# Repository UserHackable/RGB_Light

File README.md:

## RGB_Light 

### Board dimensions

* (120000, 140000) original units
* (1.2000, 1.4000) inches
* (30.4800, 35.5600) mm

[gerbers](%*_gerber.zip)

| Front | Back |
| --- | --- |
|  |  |

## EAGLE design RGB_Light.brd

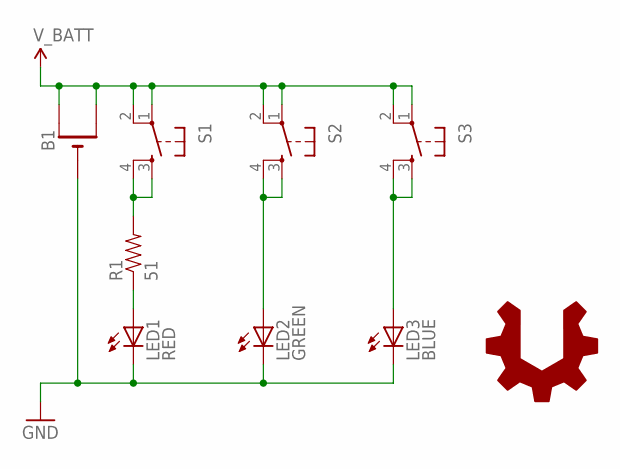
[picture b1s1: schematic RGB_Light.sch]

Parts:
B1: CR2032THM; CR2032-THRU
LED1: RED; LED5MM
LED2: GREEN; LED5MM
LED3: BLUE; LED5MM
R1: 51; AXIAL-0.3
S1, S2, S3: TAC_SWITCHPTH; TACTILE-PTH
U$1: USER_HACKABLE

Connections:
GND: B1.-, LED1.K (C), LED2.K (C), LED3.K (C)
unnamed: LED2.A, S2.3, S2.4
unnamed: R1.P$2 (2), S1.3, S1.4
unnamed: LED3.A, S3.3, S3.4
unnamed: LED1.A, R1.P$1 (1)
V_BATT: B1.+1 (+), B1.+2 (+1), S1.1, S1.2, S2.1, S2.2, S3.1, S3.2

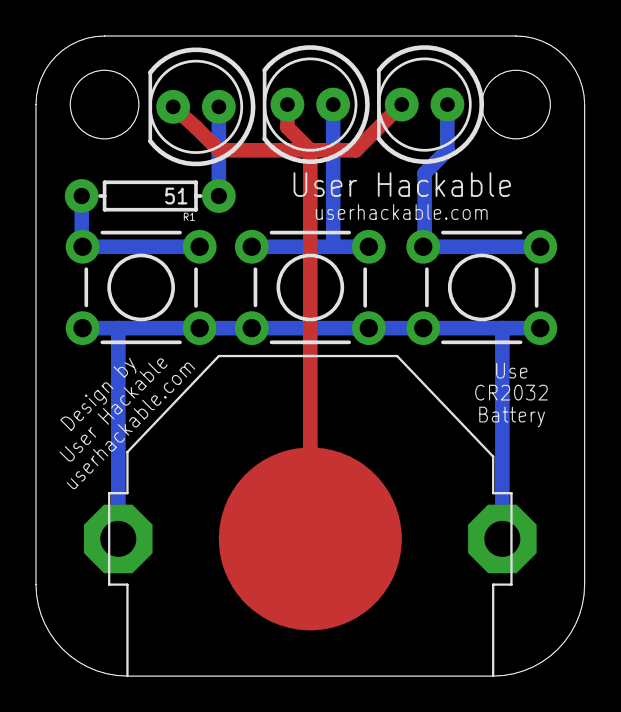
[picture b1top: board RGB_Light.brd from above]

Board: 2 copper layers, 30.5 x 35.6 mm, 9 parts (1 on the bottom side), 6 nets.

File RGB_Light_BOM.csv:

No.,Digikey part number,Description,MFG Part Number,Manufacturer,Package,Value,Qty,RefDefs,Type,Note
1, 450-1804-ND, SWITCH TACTILE SPST-NO 0.05A 24V,1825910-7,TE Connectivity Alcoswitch Switches,6.00mm x 6.00mm,SPST-NO,3,"S1,S2,S3",Thru-Hole,Any Tactile Switch with matching footprint will work
2, BK-913-ND, RETAINER CR2032 WITH PC PINS,BK-913,MPD (Memory Protection Devices),CR2032,,1,B1,Thru-Hole,
3, CF14JT51R0CT-ND, RES 51 OHM 1/4W 5% CARBON FILM,CF14JT51R0,Stackpole Electronics Inc.,1/4W 5%,51 Ohm,1,R1,Thru-Hole,Any 51 ohm 5% ¼ watt through hole resistor will work.
4, N189-ND, BATTERY LITHIUM 3V COIN 20MM,CR2032VP,Energizer Battery Company,CR2032,3v,1,,,Any CR2032 Battery works – DNP.. part of kit when sold retail. 
5,,Red LED,,Cree,4mm oval,,1,LED1,Thru-Hole,Surplus
6,,Blue LED,,Cree,4mm oval,,1,LED3,Thru-Hole,Surplus
7,,Green LED,,Cree,4mm oval,,1,LED2,Thru-Hole,Surplus

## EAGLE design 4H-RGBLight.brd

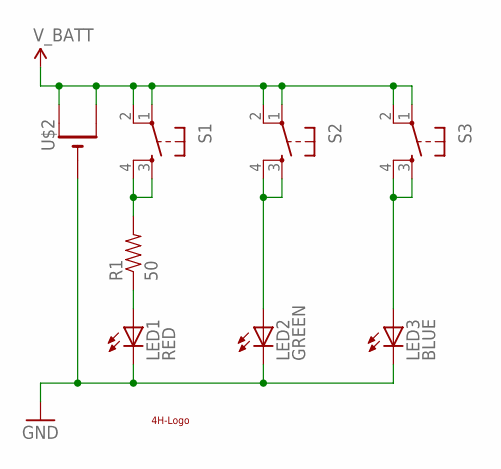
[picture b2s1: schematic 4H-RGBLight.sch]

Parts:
LED1: RED; LED-OVAL
LED2: GREEN; LED-OVAL
LED3: BLUE; LED-OVAL
R1: 50; AXIAL-0.3
S1, S2, S3: TAC_SWITCHPTH; TACTILE-PTH
U$2: CR2032THM; CR2032-THRU
U$3: 4H-LOGO6; 4H_LOGO_6

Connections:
GND: LED1.CATHODE (C), LED2.CATHODE (C), LED3.CATHODE (C), U$2.-
unnamed: LED2.ANODE (A), S2.3, S2.4
unnamed: R1.P$2 (2), S1.3, S1.4
unnamed: LED3.ANODE (A), S3.3, S3.4
unnamed: LED1.ANODE (A), R1.P$1 (1)
V_BATT: S1.1, S1.2, S2.1, S2.2, S3.1, S3.2, U$2.+1 (+), U$2.+2 (+1)

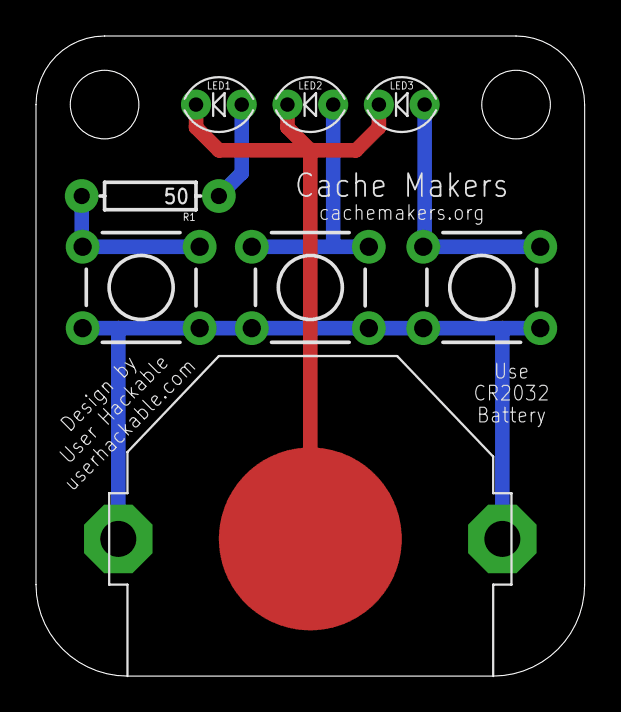
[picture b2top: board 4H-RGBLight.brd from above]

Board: 2 copper layers, 30.5 x 35.6 mm, 9 parts (1 on the bottom side), 6 nets.

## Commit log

2016-04-07 from Makefile
2016-04-29 adding in BOM
2016-04-29 updating bom

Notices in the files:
parts and their libraries:
SparkFun-Aesthetics: Licensing: Creative Commons ShareAlike 4.0 International - https://creativecommons.org/licenses/by-sa/4.0
